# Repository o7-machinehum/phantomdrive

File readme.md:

[>>> Buy Hardware <<<](https://shop.rootkitlabs.com/products/phantomdrive)

Phantomdrive is open source encrypted USB drive with a stealth mechanism to hide its second partition. To decrypt it you must create a file containing your password in the format `password:addpasswordhere`, this is used to derive AES-XTS keys. The drive automatically unmounts itself, remounts the remaining disk and encrypts and decrypts in place. It uses CH569W SoC, which has USB3, SDIO and an AES hardware block. It is programmable over USB using the `wch-ch56x-isp` library.

``` bash
|-- ee             # Hardware files
|-- Makefile
|-- readme.md      # This files
|-- test           # Test the cypto components
|-- ref            # Reference docs
|-- src            # Firmware
|-- tests          # Verification scripts
|-- wch-ch56x-bsp  # Board support package
`-- wch-ch56x-isp  # Programming software
```

# Getting Started
``` bash
git submodule update --init --recursive --checkout --force
cd wch-ch56x-isp
make # Build the ISP tool
```

## Install the toolchain
The HydraUSB3 project requires the patched HydraUSB3 xPack GCC 12.2.0-1, which
supports the `WCH-Interrupt-fast` interrupt attribute:

```bash
cd /tmp
curl -sL -o riscv-gcc-xpack.tar.gz \
  "https://github.com/hydrausb3/riscv-none-elf-gcc-xpack/releases/download/12.2.0-1/xpack-riscv-none-elf-gcc-12.2.0-1-linux-x64.tar.gz"
tar xzf riscv-gcc-xpack.tar.gz
sudo cp -r xpack-riscv-none-elf-gcc-12.2.0-1/* /usr/local/
```

## Debugging
```
make UART=1 # Enable UART
```

## Build and Flashing the project

The AES mode, PBKDF2 iteration count, and locked capacity can be selected
independently. Supported KDF values are `100000` and `600000`; 100,000 is the
default. `LOCKED_SECTORS` sets the locked (decoy) capacity in 512-byte sectors
and defaults to 16,777,216 sectors (8 GiB). It must be smaller than the physical
card's sector count; otherwise the unlocked capacity calculation underflows.

``` bash
# Remove flash drive
# While holding boot button, plug in

# Build and flash AES-XTS firmware with 600,000 PBKDF2 iterations and an
# 8 GiB locked capacity
make AES_MODE=XTS KDF_ROUNDS=600000 LOCKED_SECTORS=16777216 flash

# Or build and flash AES-CTR firmware with 100,000 iterations
make AES_MODE=CTR KDF_ROUNDS=100000 flash

# Build all four AES/KDF combinations
./release.sh
```

The four builds are written to `build/CTR_100K`, `build/CTR_600K`,
`build/XTS_100K`, and `build/XTS_600K`.

## Unlocking Drive
``` bash
# This will keep your password in bash history, but fine for testing/insecure
sudo echo "password:YourPasswordHere13245" > /mnt/unlock.txt

# Or avoid keeping the password is bash history
sudo dd of=/mnt/unlock.txt
password:YourPasswordHere13245
^D # ctrl+d
```
On the same note, please ensure your text editor doesn't cash/backup files, if they do disable that or use a different editor.

# Releasing the hardware
``` bash
./scripts/release_hardware.sh
```

# Security Notes

This code has not been professionally audited. Treat Phantomdrive as an experimental open source hardware/firmware project rather than a formally reviewed security product. The current level of validation is described in the [test README](test/readme.md). I am not responsible for loss of data, security incidents, or other damage resulting from use of this project.

The encrypted area can use AES-256-CTR or AES-256-XTS, with keys derived using
PBKDF2-HMAC-SHA256 and either 100,000 or 600,000 iterations. AES mode and KDF
iteration count affect the on-disk format, so firmware built with different
settings cannot decrypt the same data without migration or reformatting.

Unlocking accepts any file of up to 256 bytes in the root directory containing `password:YourPassword`; `password:` is reserved across the locked volume, and values following it are captured in RAM and zeroed before SD writes. FatFs deletes the matching file before unlocking and creates FAT32 at startup if the decoy volume does not already contain FAT32.

Shells may save commands in history so be aware when unlocking from the shell. Additionally, some text editors cache file contents in swap, autosave, or recovery files, etc... If you're using a text editor to enter your password disable this feature.

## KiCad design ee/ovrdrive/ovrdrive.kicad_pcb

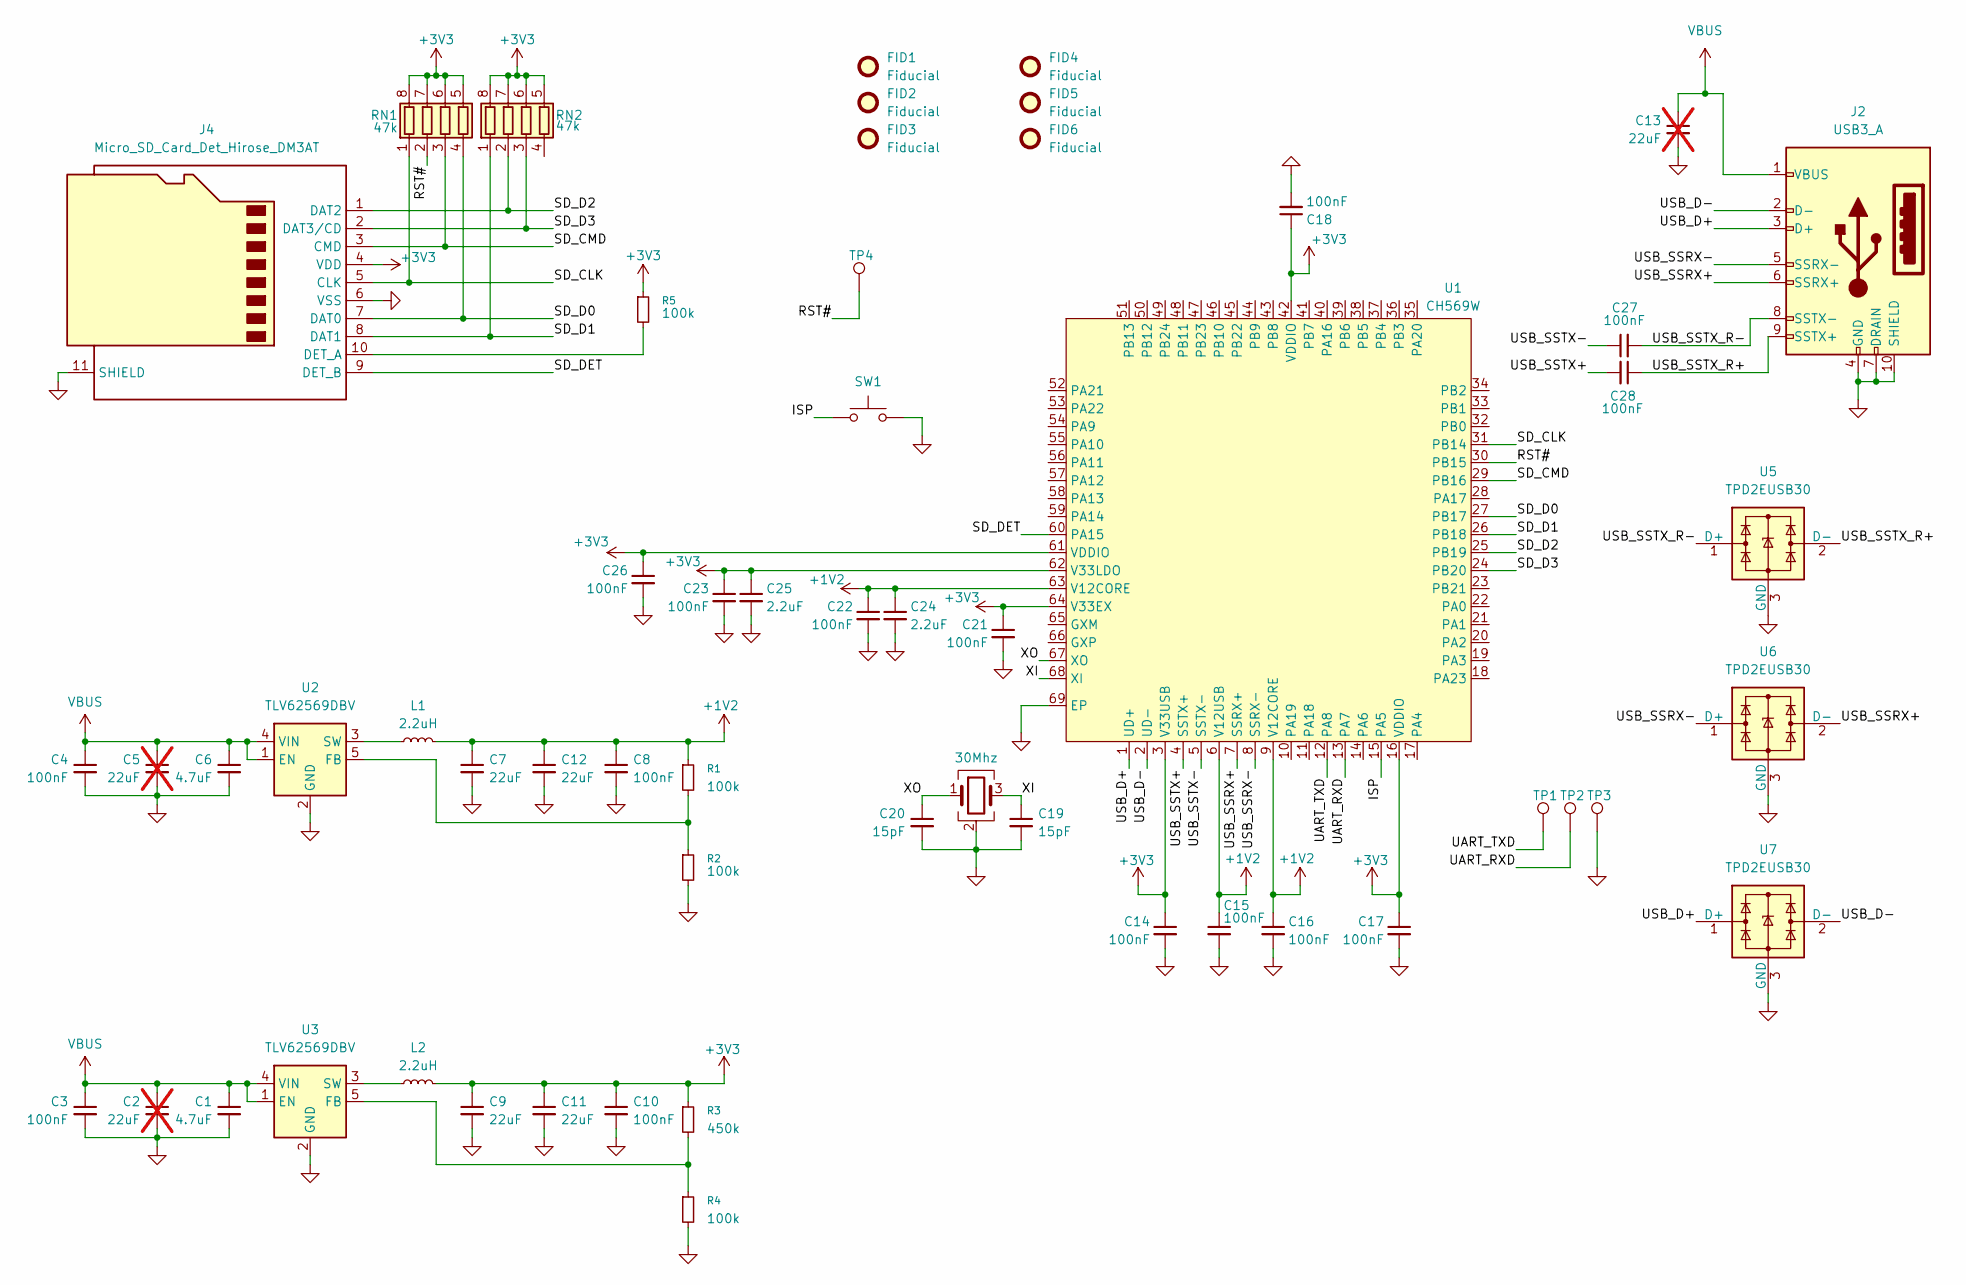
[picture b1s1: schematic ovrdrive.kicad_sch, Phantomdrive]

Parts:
C1, C6: 4.7uF; C_0402_1005Metric; MPN CL05A475MP5NRNC
C2, C5, C13: 22uF; C_0402_1005Metric; MPN CL05A226MQ5N6J8; not fitted
C3, C4, C8, C10, C14, C15, C16, C17, C18, C21, C22, C23, C26, C27, C28: 100nF; C_0402_1005Metric; MPN CL05B104KP5NNNC
C7, C9, C11, C12: 22uF; C_0402_1005Metric; MPN CL05A226MQ5N6J8
C19, C20: 15pF; C_0402_1005Metric; MPN CL05C150JB5NNNC
C24, C25: 2.2uF; C_0402_1005Metric; MPN CL05A225MQ5NNNC
FID1, FID2, FID3, FID4, FID5, FID6: Fiducial; Fiducial_0.5mm_Mask1mm; MPN DNP
J2: USB3_A; USB3_A_Plug_Wuerth_692112030100_Horizontal; MPN XUSM-0930-231
J4: Micro_SD_Card_Det_Hirose_DM3AT; microSD_HC_Hirose_DM3AT-SF-PEJM5; MPN DM3AT-SF-PEJM5
L1, L2: 2.2uH; L_Changjiang_FTC303015D; MPN SRN3015-2R2M
R1, R2, R4, R5: 100k; C_0402_1005Metric; MPN RC0402FR-07100KL
R3: 450k; C_0402_1005Metric; MPN RC0402FR-07453KL
RN1, RN2: 47k; R_Array_Concave_4x0402; MPN CAT10-473J4LF
SW1: SW_Push; SW_Push_SPST_NO_Alps_SKRK; MPN SKRKAEE020
TP1, TP2, TP3, TP4: TestPoint; TestPoint_Pad_1.0x1.0mm; MPN DNP
U1: CH569W; QFN-68-1EP_8x8mm_P0.4mm_EP5.2x5.2mm; MPN CH569W
U2, U3: TLV62569DBV; SOT-23-5; MPN TLV62569DBV
U5, U6, U7: TPD2EUSB30; Texas_DRT-3; MPN TPD2EUSB30DRTR
Y2: 30Mhz; Crystal_SMD_3225-4Pin_3.2x2.5mm; MPN ABM8-30.000MHZ-12-B1U-T

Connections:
+1V2: C7.1, C8.1, C12.1, C15.1, C16.1, C22.1, C24.1, L1.2, R1.1, U1.6 (V12USB), U1.9 (V12CORE), U1.63 (V12CORE)
+3V3: C9.1, C10.1, C11.1, C14.1, C17.1, C18.1, C21.1, C23.1, C25.1, C26.1, J4.4 (VDD), L2.2, R3.1, R5.1, RN1.5 (R4.2), RN1.6 (R3.2), RN1.7 (R2.2), RN1.8 (R1.2), RN2.5 (R4.2), RN2.6 (R3.2), RN2.7 (R2.2), RN2.8 (R1.2), U1.3 (V33USB), U1.16 (VDDIO), U1.42 (VDDIO), U1.61 (VDDIO), U1.62 (V33LDO), U1.64 (V33EX)
/ISP: SW1.1, U1.15 (PA5)
/RST#: RN1.2 (R2.1), TP4.1 (1_1), U1.30 (PB15)
/SD_CLK: J4.5 (CLK), RN1.1 (R1.1), U1.31 (PB14)
/SD_CMD: J4.3 (CMD), RN1.3 (R3.1), U1.29 (PB16)
/SD_D0: J4.7 (DAT0), RN1.4 (R4.1), U1.27 (PB17)
/SD_D1: J4.8 (DAT1), RN2.1 (R1.1), U1.26 (PB18)
/SD_D2: J4.1 (DAT2), RN2.2 (R2.1), U1.25 (PB19)
/SD_D3: J4.2 (DAT3/CD), RN2.3 (R3.1), U1.24 (PB20)
/SD_DET: J4.9 (DET_B), U1.60 (PA15)
/UART_RXD: TP2.1 (1_1), U1.13 (PA7)
/UART_TXD: TP1.1 (1_1), U1.12 (PA8)
/USB_D+: J2.3 (D+), U1.1 (UD+), U7.1 (D+)
/USB_D-: J2.2 (D-), U1.2 (UD-), U7.2 (D-)
/USB_SSRX+: J2.6 (SSRX+), U1.7 (SSRX+), U6.2 (D-)
/USB_SSRX-: J2.5 (SSRX-), U1.8 (SSRX-), U6.1 (D+)
/USB_SSTX+: C28.2, U1.4 (SSTX+)
/USB_SSTX-: C27.1, U1.5 (SSTX-)
/USB_SSTX_R+: C28.1, J2.9 (SSTX+), U5.2 (D-)
/USB_SSTX_R-: C27.2, J2.8 (SSTX-), U5.1 (D+)
/XI: C19.1, U1.68 (XI), Y2.3
/XO: C20.1, U1.67 (XO), Y2.1
GND: C1.2, C2.2, C3.2, C4.2, C5.2, C6.2, C7.2, C8.2, C9.2, C10.2, C11.2, C12.2, C13.2, C14.2, C15.2, C16.2, C17.2, C18.2, C19.2, C20.2, C21.2, C22.2, C23.2, C24.2, C25.2, C26.2, J2.4 (GND), J2.7 (DRAIN), J2.10 (SHIELD), J4.6 (VSS), J4.11 (SHIELD), R2.2, R4.2, SW1.2, TP3.1 (1_1), U1.69 (EP), U2.2 (GND), U3.2 (GND), U5.3 (GND), U6.3 (GND), U7.3 (GND), Y2.2 (G), Y2.4 (G)
unnamed: J4.10 (DET_A), R5.2
unnamed: R1.2, R2.1, U2.5 (FB)
unnamed: L1.1, U2.3 (SW)
unnamed: R3.2, R4.1, U3.5 (FB)
unnamed: L2.1, U3.3 (SW)
VBUS: C1.1, C2.1, C3.1, C4.1, C5.1, C6.1, C13.1, J2.1 (VBUS), U2.1 (EN), U2.4 (VIN), U3.1 (EN), U3.4 (VIN)

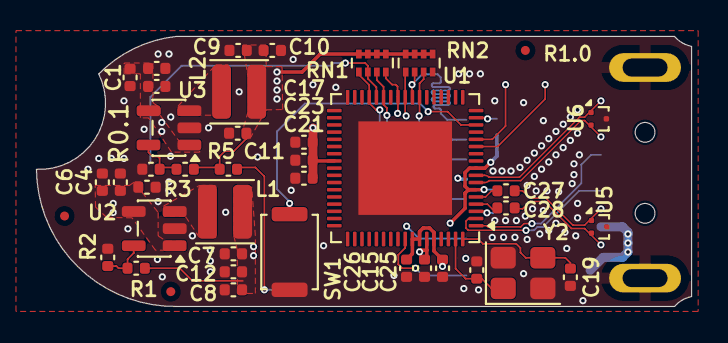
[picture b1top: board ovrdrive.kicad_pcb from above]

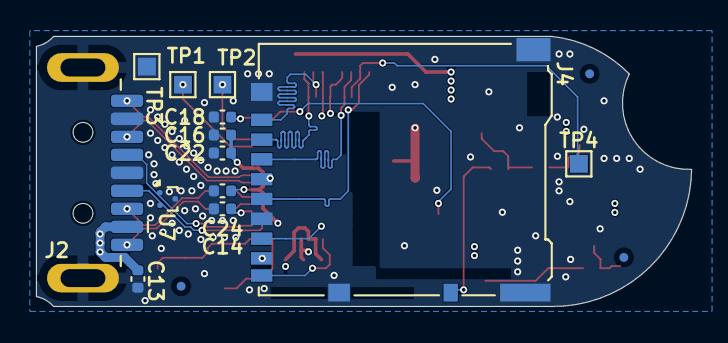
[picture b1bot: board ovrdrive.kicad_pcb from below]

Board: 4 copper layers, 36.4 x 15.0 mm, 57 parts (16 on the bottom side), 30 nets.

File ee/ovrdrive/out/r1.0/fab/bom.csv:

"Designator","Value","Footprint","Quantity","Part Number"
"C1,C6","4.7uF","Capacitor_SMD:C_0402_1005Metric","2","CL05A475MP5NRNC"
"C3,C4,C8,C10,C14-C18,C21-C23,C26-C28","100nF","Capacitor_SMD:C_0402_1005Metric","15","CL05B104KP5NNNC"
"C7,C9,C11,C12","22uF","Capacitor_SMD:C_0402_1005Metric","4","CL05A226MQ5N6J8"
"C19,C20","15pF","Capacitor_SMD:C_0402_1005Metric","2","CL05C150JB5NNNC"
"C24,C25","2.2uF","Capacitor_SMD:C_0402_1005Metric","2","CL05A225MQ5NNNC"
"J2","USB3_A","Connector_USB:USB3_A_Plug_Wuerth_692112030100_Horizontal","1","XUSM-0930-231"
"J4","Micro_SD_Card_Det_Hirose_DM3AT","Connector_Card:microSD_HC_Hirose_DM3AT-SF-PEJM5","1","DM3AT-SF-PEJM5"
"L1,L2","2.2uH","Inductor_SMD:L_Changjiang_FTC303015D","2","SRN3015-2R2M"
"R1,R2,R4,R5","100k","Capacitor_SMD:C_0402_1005Metric","4","RC0402FR-07100KL"
"R3","450k","Capacitor_SMD:C_0402_1005Metric","1","RC0402FR-07453KL"
"RN1,RN2","47k","Resistor_SMD:R_Array_Concave_4x0402","2","CAT10-473J4LF"
"SW1","SW_Push","Button_Switch_SMD:SW_Push_SPST_NO_Alps_SKRK","1","SKRKAEE020"
"U1","CH569W","Package_DFN_QFN:QFN-68-1EP_8x8mm_P0.4mm_EP5.2x5.2mm","1","CH569W"
"U2,U3","TLV62569DBV","Package_TO_SOT_SMD:SOT-23-5","2","TLV62569DBV"
"U5-U7","TPD2EUSB30","Package_TO_SOT_SMD:Texas_DRT-3","3","TPD2EUSB30DRTR"
"Y2","30Mhz","Crystal:Crystal_SMD_3225-4Pin_3.2x2.5mm","1","ABM8-30.000MHZ-12-B1U-T"

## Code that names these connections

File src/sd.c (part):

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 * (CMD17/18 for read, CMD24/25 for write).
 *
 * Hardware interface:
 *   CLK  = PB15 (bSDCK)          - SD clock output
 *   CMD  = PB14 (bSDCMD)         - SD command line (bidirectional)
 *   DAT0 = PB17                  - SD data line 0
 *   DAT1 = PB18                  - SD data line 1
 *   DAT2 = PB19                  - SD data line 2
 *   DAT3 = PB20                  - SD data line 3
 *   [CH569DS1.PDF: GPIO Pin Multiplexing, eMMC Controller]
 *
 * Clock configuration:
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	/* GPIO: Enable pull-ups on CMD and DAT lines for proper idle state
	 * SD spec requires pull-ups on CMD, DAT0-DAT3 */
	R32_PB_PU  |= bSDCMD;        /* CMD line pull-up */
	R32_PB_PU  |= (0x1f<<17);    /* DAT0-DAT4 pull-ups (PB17-PB21) */
	R32_PA_PU  |= (7<<0);        /* Additional data lines (PA0-PA2) */
	R32_PB_DIR |= bSDCK;         /* CLK line as output */

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
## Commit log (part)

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2026-05-19 Removed USB-3 path, simplified code.
2026-05-19 Removed the "link training" for the SD card.
2026-05-19 Moved the profiler into separate functions, implement ECDC
2026-05-19 Added stuff to the profiler
2026-05-24 Rename
2026-05-24 Remove self test from production code
2026-05-24 Rename function.
2026-05-24 Fixed linker script.
2026-05-24 Cleanup
2026-05-24 More cleanup
2026-05-24 Refactor to use bool so variable function is more explicit.
2026-05-24 fix: V-002 security vulnerability
    Automated security fix generated by OrbisAI Security
2026-05-24 fix: add buffer-length check in phantomdrive.c
    The password handling routine copies user-supplied password data from a USB bulk transfer buffer into a fixed-size pending_pw buffer without validating that pw_len does not exceed the destination buf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
2026-05-24 Added docs and comments.
2026-05-26 KDF test working.
2026-05-26 Add to gitignore
2026-06-09 V1.0-rc1
    The salt is now derived from the UID of the device. Debug is snubbed in a cleaner way. Tests adapted
2026-06-10 restore ECDC self-test and refuse unlock on failure
2026-06-18 Updated vendor id
2026-06-18 Updated BSP with patch.
2026-06-21 Updated readme to reflect that files does not need to be called update.txt
2026-06-21 Added notes on lack of audit and AES-CTR limitations to readme, liabilty, etc
2026-06-22 Hardware r1.0

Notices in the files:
src/sd.c:
SPDX-License-Identifier: Apache-2.0
